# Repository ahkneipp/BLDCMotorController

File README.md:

# BLDCMotorController
Implementation of a BLDC motor controller from scratch for electric skateboard build

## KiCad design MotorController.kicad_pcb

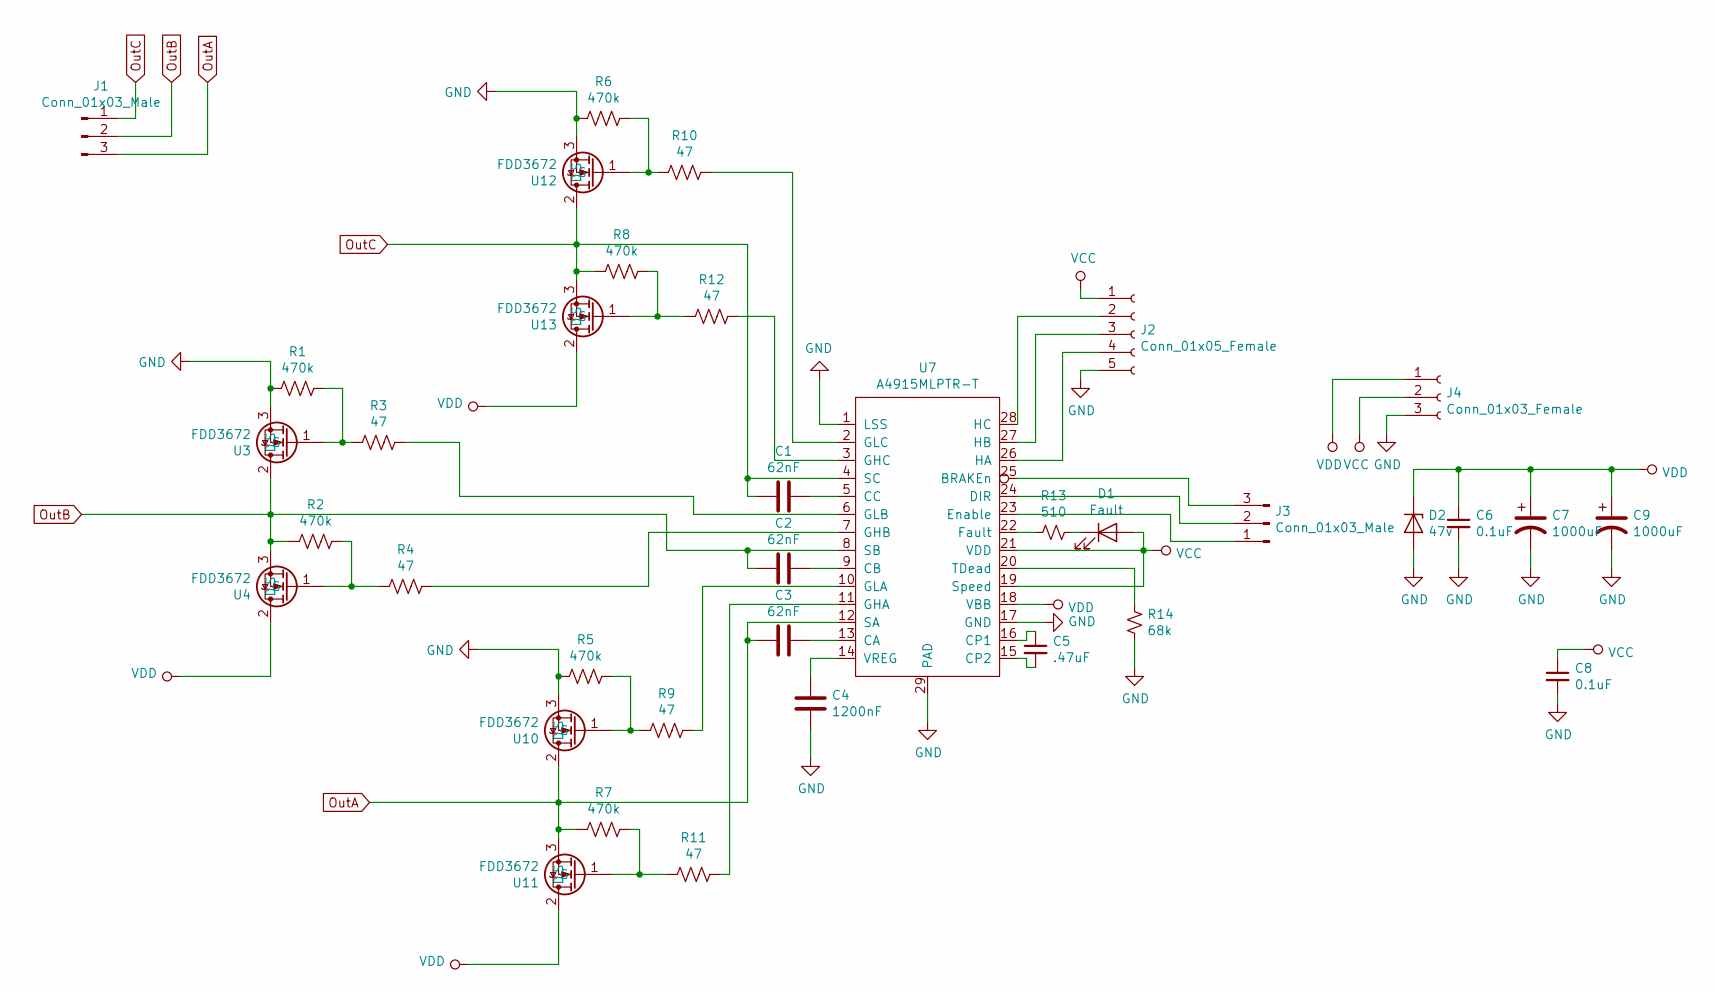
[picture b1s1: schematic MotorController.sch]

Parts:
C1, C2, C3: 62nF; C_1206_3216Metric_Pad1.42x1.75mm_HandSolder
C4: 1200nF; C_0805_2012Metric_Pad1.15x1.40mm_HandSolder
C5: .47uF; C_Disc_D4.7mm_W2.5mm_P5.00mm
C6, C8: 0.1uF; C_Disc_D4.3mm_W1.9mm_P5.00mm
C7, C9: 1000uF; CP_Radial_D12.5mm_P5.00mm
D1: Fault; LED_D5.0mm_Clear
D2: 47v; D_DO-41_SOD81_P3.81mm_Vertical_AnodeUp
J1: Conn_01x03_Male; TerminalBlock_Molex-3_P12.7mm
J2: Conn_01x05_Female; JST_PH_S5B-PH-K_1x05_P2.00mm_Horizontal
J3: Conn_01x03_Male; Molex_KK-254_AE-6410-03A_1x03_P2.54mm_Vertical
J4: Conn_01x03_Female; TerminalBlock_Molex-3_P12.7mm
R1, R2, R5, R6, R7, R8: 470k; R_Axial_DIN0204_L3.6mm_D1.6mm_P2.54mm_Vertical
R3, R4, R9, R10, R11, R12: 47; R_Axial_DIN0204_L3.6mm_D1.6mm_P2.54mm_Vertical
R13: 510; R_Axial_DIN0204_L3.6mm_D1.6mm_P2.54mm_Vertical
R14: 68k; R_Axial_DIN0204_L3.6mm_D1.6mm_P2.54mm_Vertical
U3, U4, U10, U11, U12, U13: FDD3672; TO-252-2
U7: A4915MLPTR-T; TSSOP-28-1EP_4.4x9.7mm_P0.65mm

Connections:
GND: C4.2, C6.2, C7.2, C8.2, C9.2, D2.2 (A), J2.5, J4.3, R1.2, R5.2, R6.2, R14.2, U3.3 (S), U7.1 (LSS), U7.17 (GND), U7.29 (PAD), U10.3 (S), U12.3 (S)
unnamed: C1.1, U7.5 (CC)
unnamed: C2.1, U7.9 (CB)
unnamed: C3.1, U7.13 (CA)
unnamed: C4.1, U7.14 (VREG)
unnamed: C5.1, U7.16 (CP1)
unnamed: C5.2, U7.15 (CP2)
unnamed: D1.1 (K), R13.1
unnamed: J2.2, U7.28 (HC)
unnamed: J2.3, U7.27 (HB)
unnamed: J2.4, U7.26 (HA)
unnamed: J3.1, U7.23 (Enable)
unnamed: J3.2, U7.24 (DIR)
unnamed: J3.3, U7.25 (BRAKEn)
unnamed: R1.1, R3.2, U3.1 (G)
unnamed: R2.1, R4.2, U4.1 (G)
unnamed: R3.1, U7.6 (GLB)
unnamed: R4.1, U7.7 (GHB)
unnamed: R5.1, R9.2, U10.1 (G)
unnamed: R9.1, U7.10 (GLA)
unnamed: R10.1, U7.2 (GLC)
unnamed: R6.1, R10.2, U12.1 (G)
unnamed: R11.1, U7.11 (GHA)
unnamed: R7.1, R11.2, U11.1 (G)
unnamed: R12.1, U7.3 (GHC)
unnamed: R8.1, R12.2, U13.1 (G)
unnamed: R13.2, U7.22 (Fault)
unnamed: R14.1, U7.20 (TDead)
OutA: C3.2, J1.3, R7.2, U7.12 (SA), U10.2 (D), U11.3 (S)
OutB: C2.2, J1.2, R2.2, U3.2 (D), U4.3 (S), U7.8 (SB)
OutC: C1.2, J1.1, R8.2, U7.4 (SC), U12.2 (D), U13.3 (S)
VCC: C8.1, D1.2 (A), J2.1, J4.2, U7.19 (Speed), U7.21 (VDD)
VDD: C6.1, C7.1, C9.1, D2.1 (K), J4.1, U4.2 (D), U7.18 (VBB), U11.2 (D), U13.2 (D)

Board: 2 copper layers, 36 parts (0 on the bottom side), 33 nets, no tracks yet.

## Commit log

2020-06-24 Previous work
2020-07-03 Syncing for travel
2020-07-11 I'm too tired to write a good message
2020-08-11 Sync commit
